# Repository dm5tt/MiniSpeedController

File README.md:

# Mini (RISC-V DC-Motor) Speed Controller

This project implements a compact DC motor speed controller using a RISC-V microcontroller. 

It is designed for speed control via pulse feedback from a light barrier and communicates through a serial interface. Additional  sensors can be attached using I2C.

Beware that the entire PCB isn't a masterpiece as this is just for technology evaluation. 

## Why this thing?

Mostly for playing around with very cheap RISC-V microcontrollers and an execise for C/Rust with very limited resources. It can be used for controlling simple toy robot chassis that usually have two DC motors with light barriers which can be used as feedback loop for a speed control algorithm.

## System Overview

#### Power Supply
  - AP62300 (3A Buck Converter) → 7V rail (for DC motors)  
  - AMS1117-3.3 (LDO Regulator) → 3.3V rail (for microcontroller and motor driver logic)  

#### WCH CH32V003 Microcontroller 
  - 48 MHz RISC-V core  
  - 16 KB Flash / 2 KB SRAM  
  - Powered from 3.3V rail
    
#### Texas Instruments DRV8837GSGR 
  - Brushed DC motor driver  
  - 1.8A continuous current capability  
  - Logic powered from 3.3V rail
  - DC motors powered from 7V rail

### Pin Configuration

#### Motor Controller 1
| Pin | Meaning          |
|-----|------------------|
| PC5 | motcon1_sleep    |
| PC6 | motcon1_in2      |
| PD2 | motcon1_pwm_in1  |

#### Motor Controller 2
| Pin | Meaning          |
|-----|------------------|
| PC3 | motcon2_sleep    |
| PC4 | motcon2_in2      |
| PA1 | motcon2_pwm_in1  |

#### PWM Speed Inputs
| Pin | Meaning          |
|-----|------------------|
| PC0 | pwm_speed_input1 |
| PD3 | pwm_speed_input2 |

#### Communication Interfaces
| Pin | Meaning          |
|-----|------------------|
| PC1 | i2c_sda          |
| PC2 | i2c_scl          |
| PD5 | usart_tx         |
| PD6 | usart_rx         |

#### Debug & Reset
| Pin | Meaning          |
|-----|------------------|
| PD1 | SWDIO            |
| PD7 | nRST             |

#### Indicators
| Pin | Meaning          |
|-----|------------------|
| PA2 | status_led       |

### Unused / Spare
| Pin | Meaning          |
|-----|------------------|
| PC7 | X                |
| PD0 | X                |
| PD4 | X                |

# Verification

[Hardware Verification v0.4](EVALUATION-v0.4.md)

# License

CERN OHL v2 – Strongly Reciprocal (S)

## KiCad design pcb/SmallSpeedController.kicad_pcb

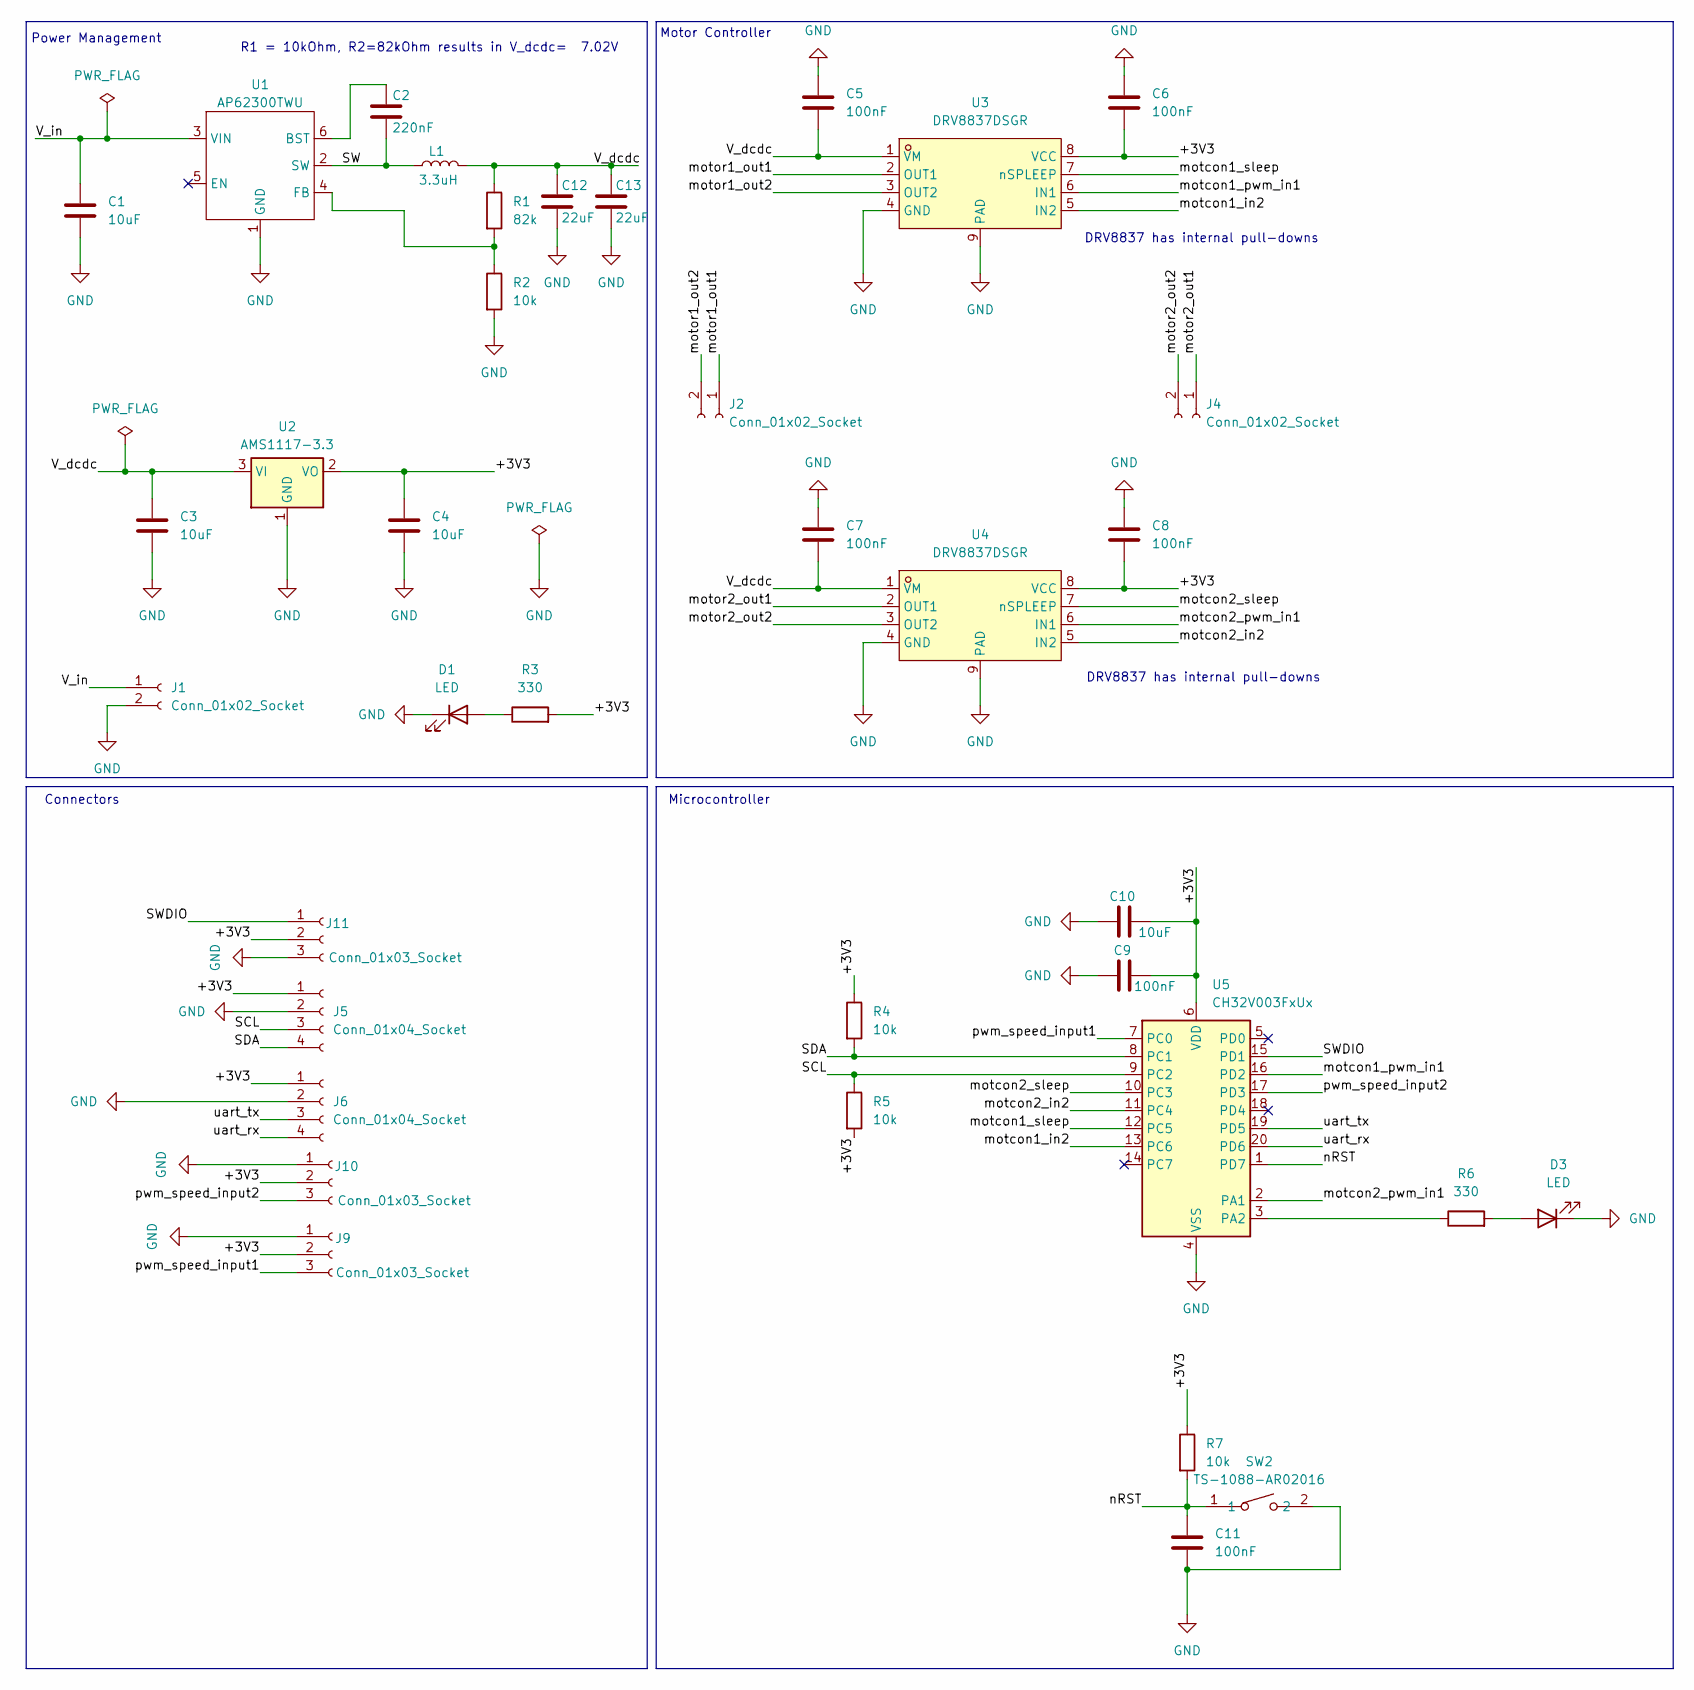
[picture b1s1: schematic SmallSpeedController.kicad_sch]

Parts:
C1, C3, C4, C10: 10uF; C_0805_2012Metric_Pad1.18x1.45mm_HandSolder
C2: 220nF; C_0805_2012Metric_Pad1.18x1.45mm_HandSolder
C5, C6, C7, C8, C9, C11: 100nF; C_0805_2012Metric_Pad1.18x1.45mm_HandSolder
C12, C13: 22uF; C_0805_2012Metric_Pad1.18x1.45mm_HandSolder
D1, D3: LED; LED_0805_2012Metric
J1, J2, J4: Conn_01x02_Socket; JST_PH_B2B-PH-K_1x02_P2.00mm_Vertical
J5, J6: Conn_01x04_Socket; JST_PH_B4B-PH-K_1x04_P2.00mm_Vertical
J9, J10, J11: Conn_01x03_Socket; JST_PH_B3B-PH-K_1x03_P2.00mm_Vertical
L1: 3.3uH; CPX0420
R1: 82k; R_0805_2012Metric_Pad1.20x1.40mm_HandSolder
R2, R4, R5, R7: 10k; R_0805_2012Metric_Pad1.20x1.40mm_HandSolder
R3, R6: 330; R_0805_2012Metric_Pad1.20x1.40mm_HandSolder
SW2: TS-1088-AR02016; SW-SMD_L3.9-W3.0-P4.45; LCSC Part C720477
U1: AP62300TWU; TSOT-23-6_HandSoldering
U2: AMS1117-3.3; SOT-223-3_TabPin2
U3, U4: DRV8837DSGR; WSON-8_L2.0-W2.0-P0.50-TL-EP; LCSC Part C39159
U5: CH32V003FxUx; QFN-20-1EP_3x3mm_P0.4mm_EP1.65x1.65mm

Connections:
/+3V3: C4.1, C6.2, C8.2, C9.2, C10.2, J5.1, J6.1, J9.2, J10.2, J11.2, R3.2, R4.1, R5.2, R7.1, U2.2 (VO), U3.8 (VCC), U4.8 (VCC), U5.6 (VDD)
/SCL: J5.3, R5.1, U5.9 (PC2)
/SDA: J5.4, R4.2, U5.8 (PC1)
/SW: C2.2, L1.1, U1.2 (SW)
/SWDIO: J11.1, U5.15 (PD1)
/V_dcdc: C3.1, C5.2, C7.2, C12.1, C13.1, L1.2, R1.1, U2.3 (VI), U3.1 (VM), U4.1 (VM)
/V_in: C1.1, J1.1, U1.3 (VIN)
/motcon1_in2: U3.5 (IN2), U5.13 (PC6)
/motcon1_pwm_in1: U3.6 (IN1), U5.16 (PD2)
/motcon1_sleep: U3.7 (nSPLEEP), U5.12 (PC5)
/motcon2_in2: U4.5 (IN2), U5.11 (PC4)
/motcon2_pwm_in1: U4.6 (IN1), U5.2 (PA1)
/motcon2_sleep: U4.7 (nSPLEEP), U5.10 (PC3)
/motor1_out1: J2.1, U3.2 (OUT1)
/motor1_out2: J2.2, U3.3 (OUT2)
/motor2_out1: J4.1, U4.2 (OUT1)
/motor2_out2: J4.2, U4.3 (OUT2)
/nRST: C11.1, R7.2, SW2.1, U5.1 (PD7)
/pwm_speed_input1: J9.3, U5.7 (PC0)
/pwm_speed_input2: J10.3, U5.17 (PD3)
/uart_rx: J6.4, U5.20 (PD6)
/uart_tx: J6.3, U5.19 (PD5)
GND: C1.2, C3.2, C4.2, C5.1, C6.1, C7.1, C8.1, C9.1, C10.1, C11.2, C12.2, C13.2, D1.1 (K), D3.1 (K), J1.2, J5.2, J6.2, J9.1, J10.1, J11.3, R2.2, SW2.2, U1.1 (GND), U2.1 (GND), U3.4 (GND), U3.9 (PAD), U4.4 (GND), U4.9 (PAD), U5.4 (VSS), U5.21 (VSS)
unnamed: D1.2 (A), R3.1
unnamed: D3.2 (A), R6.2
unnamed: C2.1, U1.6 (BST)
unnamed: R1.2, R2.1, U1.4 (FB)
unnamed: R6.1, U5.3 (PA2)

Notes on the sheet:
Microcontroller
Motor Controller
DRV8837 has internal pull-downs
R1 = 10kOhm, R2=82kOhm results in V_dcdc= 7.02V
Power Management
Connectors

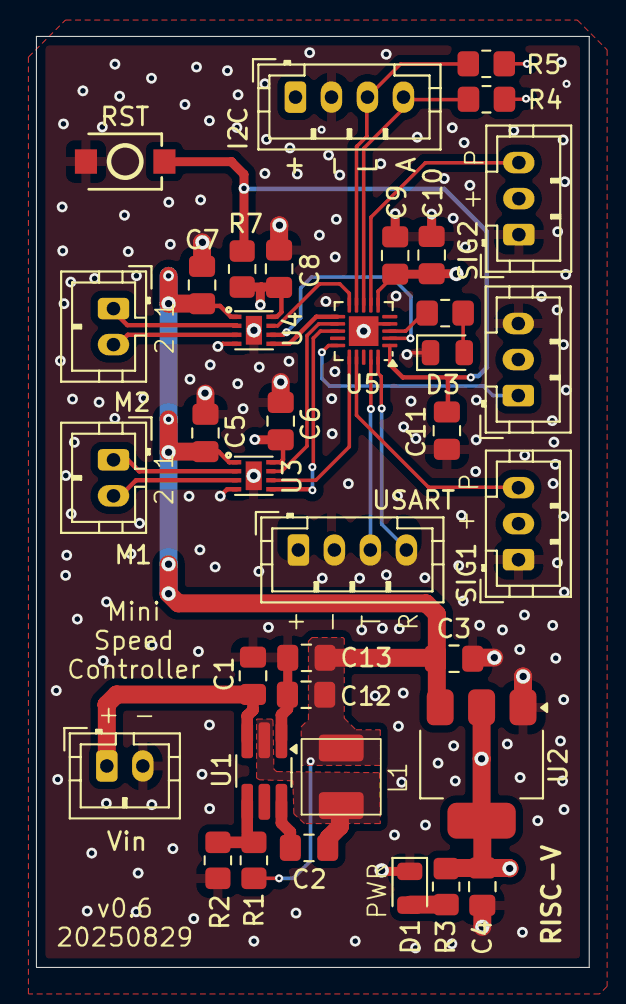
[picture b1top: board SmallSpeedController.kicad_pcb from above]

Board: 4 copper layers, 30.7 x 51.7 mm, 37 parts (0 on the bottom side), 28 nets.

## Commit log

2025-05-28 pcb, sch: small cleanups for next fabrication round
2025-05-28 README: fix typo
2025-05-28 README: add picture of schematic
2025-05-28 pcb: move silk prints around
2025-05-28 README: be more verbose about the usecase
2025-06-21 README: redo some formatting
2025-06-22 README: Microcontroller successfully verified
2025-06-22 README: add pretty picture
2025-06-22 README: replace picture
2025-06-22 README: Fix picture mess
2025-06-24 pcb: smaller board optimizations, no functional changes
2025-08-23 LICENSE: make it GPLv3
2025-08-23 src, hardwarevalidation: led and motor 2 working
2025-08-23 EVALUATION: finish evaluation
2025-08-25 README: precision -> speed
2025-08-25 README: be more precise about the light barrier
2025-08-25 minispeedcontroller, led: remove broken test code
2025-08-25 README: remove optional heading
2025-08-29 pcb: give 3v3 on the UART connector and get rid of diode
2025-08-29 pcb: harmonize silk prints, also use double vias for 7V rails
2025-08-29 pcb: non functional changes
2025-08-29 pictures: update pcb picture
2025-08-29 pcb: restore symmetry after diode was removed
2025-09-10 README: rewrite a few port definitions
2025-10-03 README: add information regarding control algorithm
2025-10-05 pictures, README: remove metadata and add picture of robot
